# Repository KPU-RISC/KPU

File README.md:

# KPU - the RISC based Open Source CPU
This repository contains complete source code and buillding files for the KPU - a RISC based CPU (Central Processing Unit). The whole CPU is emulated, simulated, and modelled on the lowest level only with primitive AND, OR, XOR, and NOT gates.

It implements a 8-bit wide Data Bus, and a 16-bit wide Address Bus. The following 8-bit wide registers are implemented:
<ul>
<li><b>D</b> (General Purpose)</li>
<li><b>E</b> (General Purpose)</li>
<li><b>F</b> (General Purpose)</li>
<li><b>G</b> (General Purpose)</li>
<li><b>H</b> (General Purpose)</li>
<li><b>XL</b> (Lower part of the 16-bit wide "X" register</li>
<li><b>XH</b> (Upper part of the 16-bit wide "X" register</li>
</ul>

The following 16-bit wide registers are implemented:
<ul>
<li><b>SP</b> (Stack Pointer)</li>
<li><b>BP</b> (Base Pointer)</li>
<li><b>PC</b> (Program Counter)</li>
<li><b>M</b> (Memory Addressing)</li>
<li><b>J</b> (Jump Destination Addressing)</li>
<li><b>X</b> (General Purpose)</li>
<li><b>Y</b> (General Purpose)</li>
<li><b>Z</b> (General Purpose)</li>
</ul>

The project contains the following sub components:
<ul>
<li><b>Assembler</b>: The Assembler generates from the assembly language binary code that can be executed by the CPU. It is written in C#, and uses ANTLR for the syntax processing.</li>
<li><b>Emulation</b>: The C#-based Emulator is able to run binary code in a Console application or within a WinForms application (used for debugging purposes).</li>
<li><b>VHDL</b>: This folder contains the whole CPU implementation as VHDL description files.</li>
<li><b>Eagle</b>: This folder contains the whole schematics and board files ready for a physical implementation of the CPU based on 74LS TTL logic chips.</li>
<li><b>Logicly</b>: This folder contains early Proof-Of-Concept files for the Logicly simulation program.</li>
</ul>

For more detailed technical information about the CPU, please visit the project website at http://www.cpu-design.at

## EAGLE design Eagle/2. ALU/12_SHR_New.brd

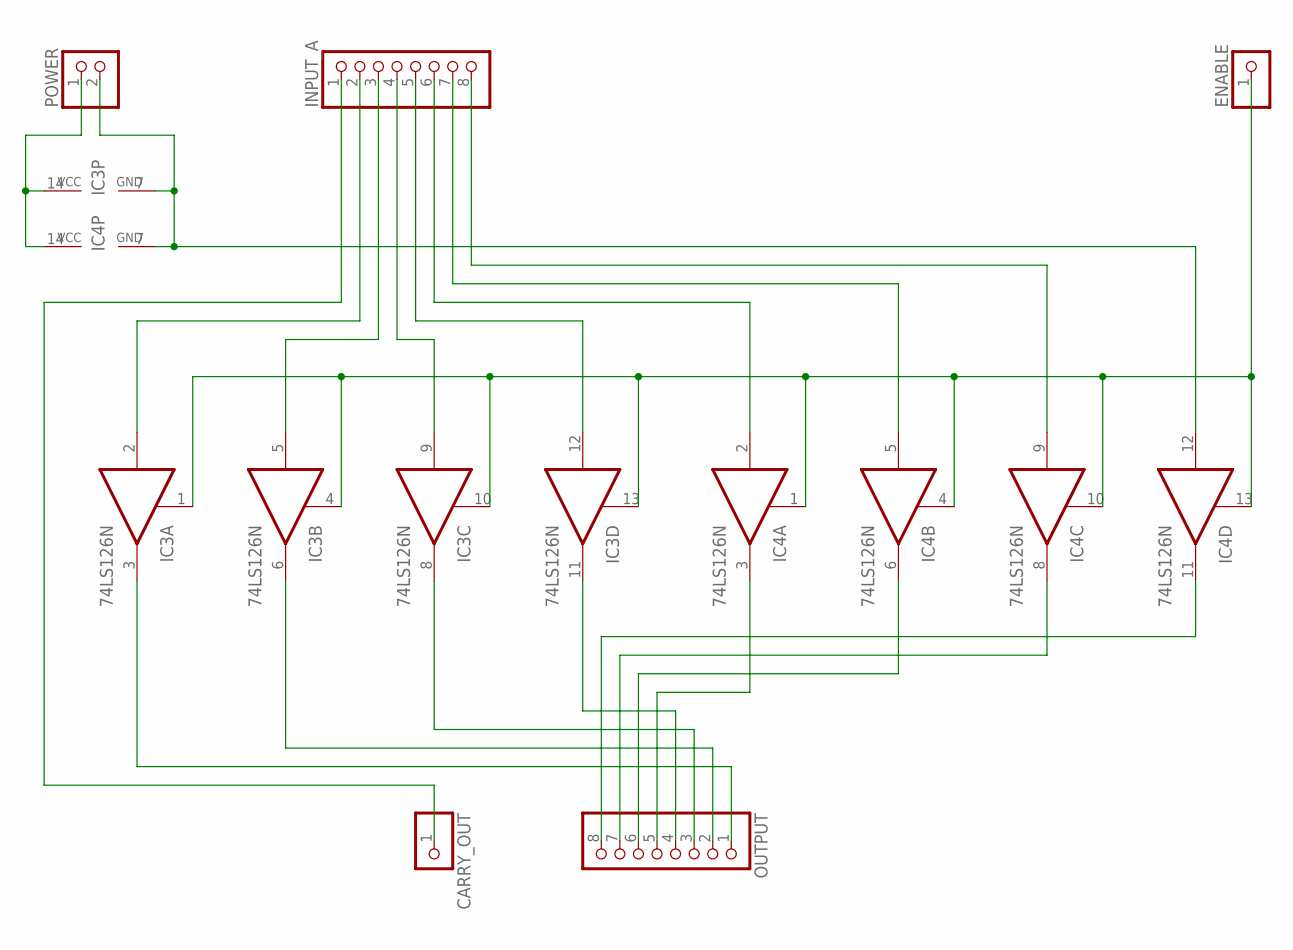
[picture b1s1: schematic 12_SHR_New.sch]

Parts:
CARRY_OUT: PINHD-1X1; 1X01
ENABLE: PINHD-1X1; 1X01
IC3, IC4: 74LS126N; DIL14
INPUT_A: PINHD-1X8; 1X08
OUTPUT: PINHD-1X8; 1X08
POWER: PINHD-1X2; 1X02

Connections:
GND: IC3.7 (GND), IC4.7 (GND), IC4.12 (I), POWER.2
unnamed: CARRY_OUT.1, INPUT_A.1
unnamed: IC3.2 (I), INPUT_A.2
unnamed: IC3.12 (I), INPUT_A.5
unnamed: IC4.2 (I), INPUT_A.6
unnamed: IC4.5 (I), INPUT_A.7
unnamed: IC4.9 (I), INPUT_A.8
unnamed: IC3.5 (I), INPUT_A.3
unnamed: IC3.9 (I), INPUT_A.4
unnamed: IC3.3 (O), OUTPUT.1
unnamed: IC3.6 (O), OUTPUT.2
unnamed: IC3.8 (O), OUTPUT.3
unnamed: IC3.11 (O), OUTPUT.4
unnamed: IC4.3 (O), OUTPUT.5
unnamed: IC4.6 (O), OUTPUT.6
unnamed: IC4.8 (O), OUTPUT.7
unnamed: IC4.11 (O), OUTPUT.8
unnamed: ENABLE.1, IC3.1 (OE), IC3.4 (OE), IC3.10 (OE), IC3.13 (OE), IC4.1 (OE), IC4.4 (OE), IC4.10 (OE), IC4.13 (OE)
VCC: IC3.14 (VCC), IC4.14 (VCC), POWER.1

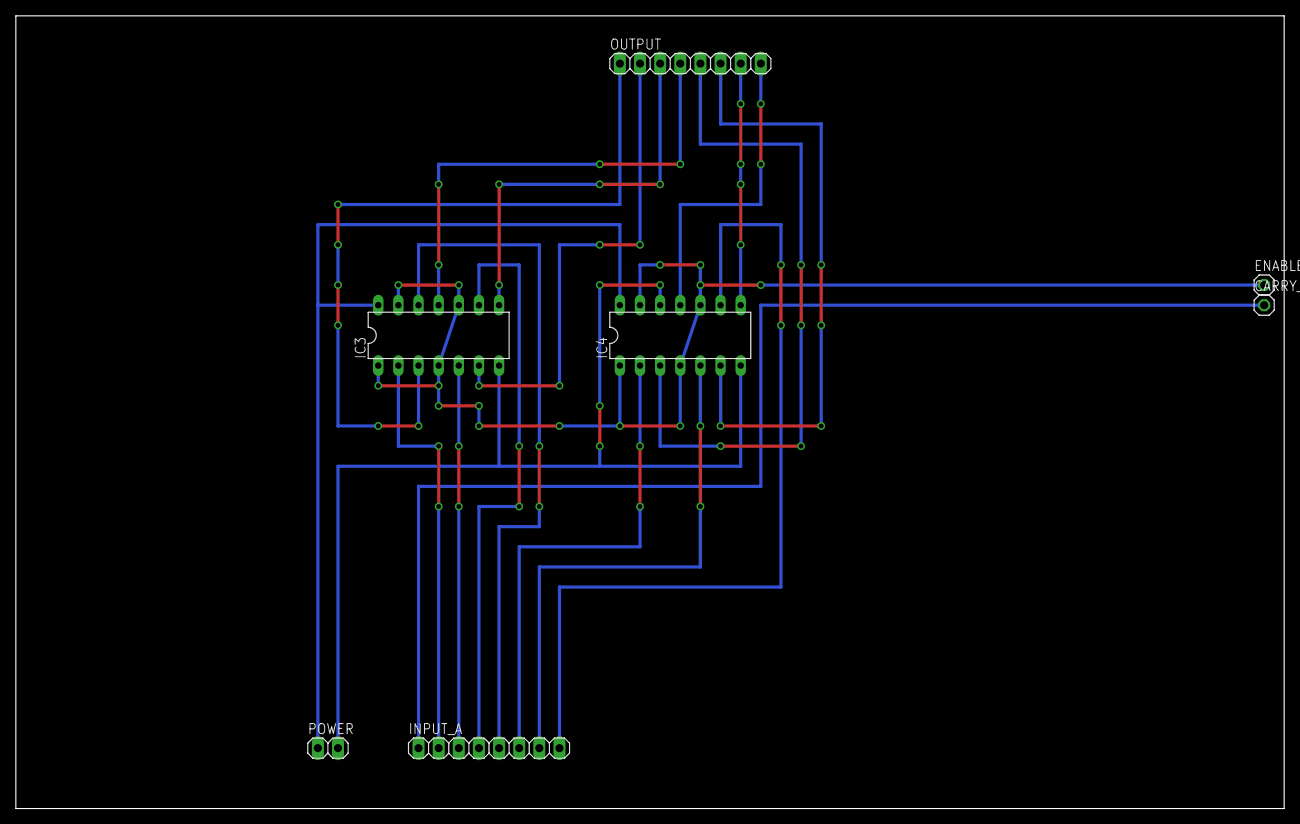
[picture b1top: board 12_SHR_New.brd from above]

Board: 2 copper layers, 160.0 x 100.0 mm, 7 parts (0 on the bottom side), 19 nets.

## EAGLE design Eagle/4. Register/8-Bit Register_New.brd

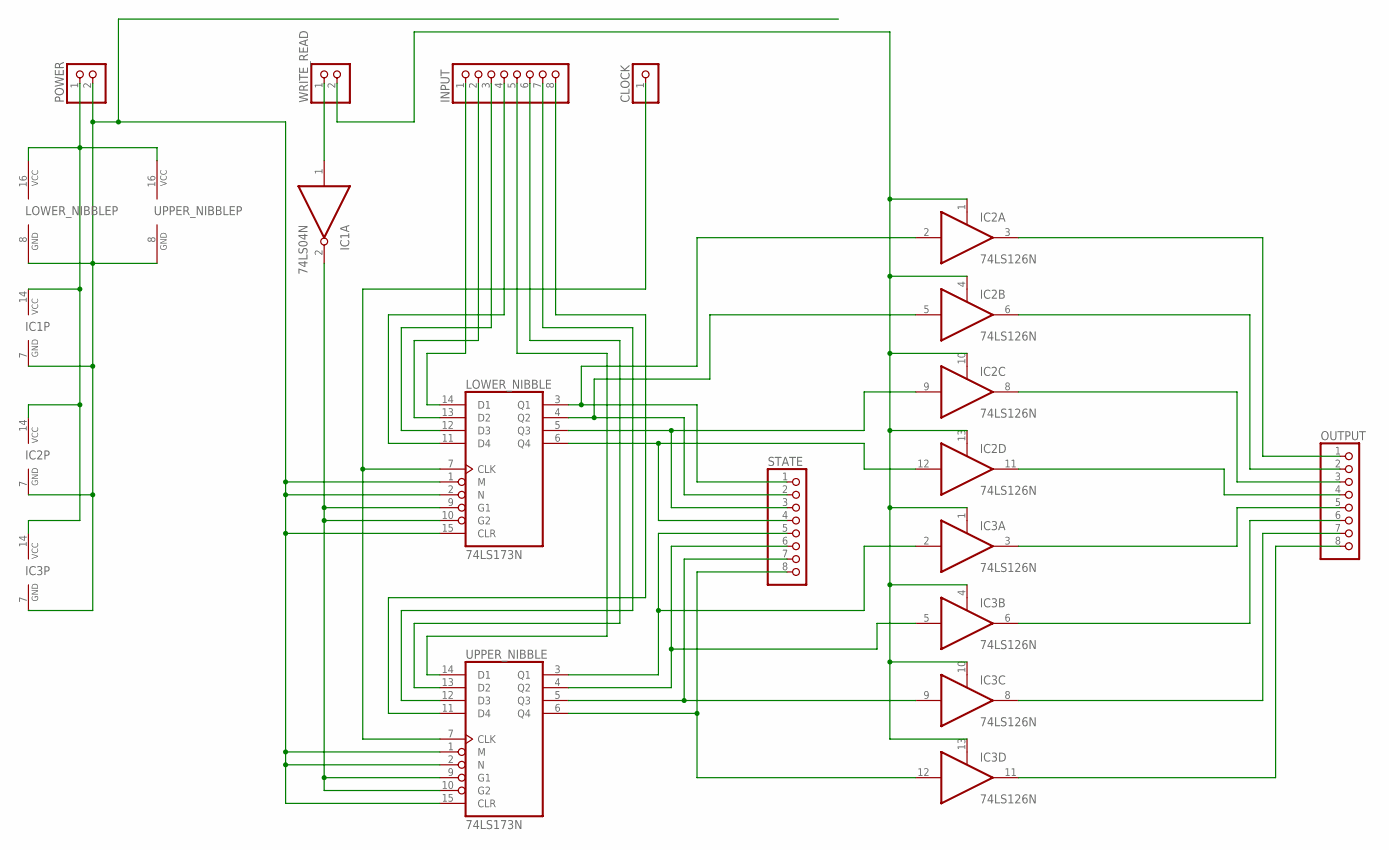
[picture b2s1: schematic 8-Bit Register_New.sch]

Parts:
CLOCK: PINHD-1X1; 1X01
IC1: 74LS04N; DIL14
IC2, IC3: 74LS126N; DIL14
INPUT: PINHD-1X8; 1X08
LOWER_NIBBLE: 74LS173N; DIL16
OUTPUT: PINHD-1X8; 1X08
POWER: PINHD-1X2; 1X02
STATE: PINHD-1X8; 1X08
UPPER_NIBBLE: 74LS173N; DIL16
WRITE_READ: PINHD-1X2; 1X02

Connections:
GND: IC1.7 (GND), IC2.7 (GND), IC3.7 (GND), LOWER_NIBBLE.1 (M), LOWER_NIBBLE.2 (N), LOWER_NIBBLE.8 (GND), LOWER_NIBBLE.15 (CLR), POWER.2, UPPER_NIBBLE.1 (M), UPPER_NIBBLE.2 (N), UPPER_NIBBLE.8 (GND), UPPER_NIBBLE.15 (CLR)
unnamed: IC2.12 (I), LOWER_NIBBLE.6 (Q4), STATE.4
unnamed: IC1.1 (I), WRITE_READ.1
unnamed: IC3.9 (I), STATE.7, UPPER_NIBBLE.5 (Q3)
unnamed: IC2.11 (O), OUTPUT.4
unnamed: IC1.2 (O), LOWER_NIBBLE.9 (G1), LOWER_NIBBLE.10 (G2), UPPER_NIBBLE.9 (G1), UPPER_NIBBLE.10 (G2)
unnamed: CLOCK.1, LOWER_NIBBLE.7 (CLK), UPPER_NIBBLE.7 (CLK)
unnamed: INPUT.1, LOWER_NIBBLE.14 (D1)
unnamed: INPUT.2, LOWER_NIBBLE.13 (D2)
unnamed: INPUT.3, LOWER_NIBBLE.12 (D3)
unnamed: INPUT.4, LOWER_NIBBLE.11 (D4)
unnamed: INPUT.6, UPPER_NIBBLE.13 (D2)
unnamed: INPUT.5, UPPER_NIBBLE.14 (D1)
unnamed: INPUT.7, UPPER_NIBBLE.12 (D3)
unnamed: INPUT.8, UPPER_NIBBLE.11 (D4)
unnamed: IC2.2 (I), LOWER_NIBBLE.3 (Q1), STATE.1
unnamed: IC2.5 (I), LOWER_NIBBLE.4 (Q2), STATE.2
unnamed: IC2.9 (I), LOWER_NIBBLE.5 (Q3), STATE.3
unnamed: IC3.2 (I), STATE.5, UPPER_NIBBLE.3 (Q1)
unnamed: IC3.5 (I), STATE.6, UPPER_NIBBLE.4 (Q2)
unnamed: IC3.12 (I), STATE.8, UPPER_NIBBLE.6 (Q4)
unnamed: IC2.1 (OE), IC2.4 (OE), IC2.10 (OE), IC2.13 (OE), IC3.1 (OE), IC3.4 (OE), IC3.10 (OE), IC3.13 (OE), WRITE_READ.2
unnamed: IC2.3 (O), OUTPUT.1
unnamed: IC2.6 (O), OUTPUT.2
unnamed: IC2.8 (O), OUTPUT.3
unnamed: IC3.3 (O), OUTPUT.5
unnamed: IC3.6 (O), OUTPUT.6
unnamed: IC3.8 (O), OUTPUT.7
unnamed: IC3.11 (O), OUTPUT.8
VCC: IC1.14 (VCC), IC2.14 (VCC), IC3.14 (VCC), LOWER_NIBBLE.16 (VCC), POWER.1, UPPER_NIBBLE.16 (VCC)

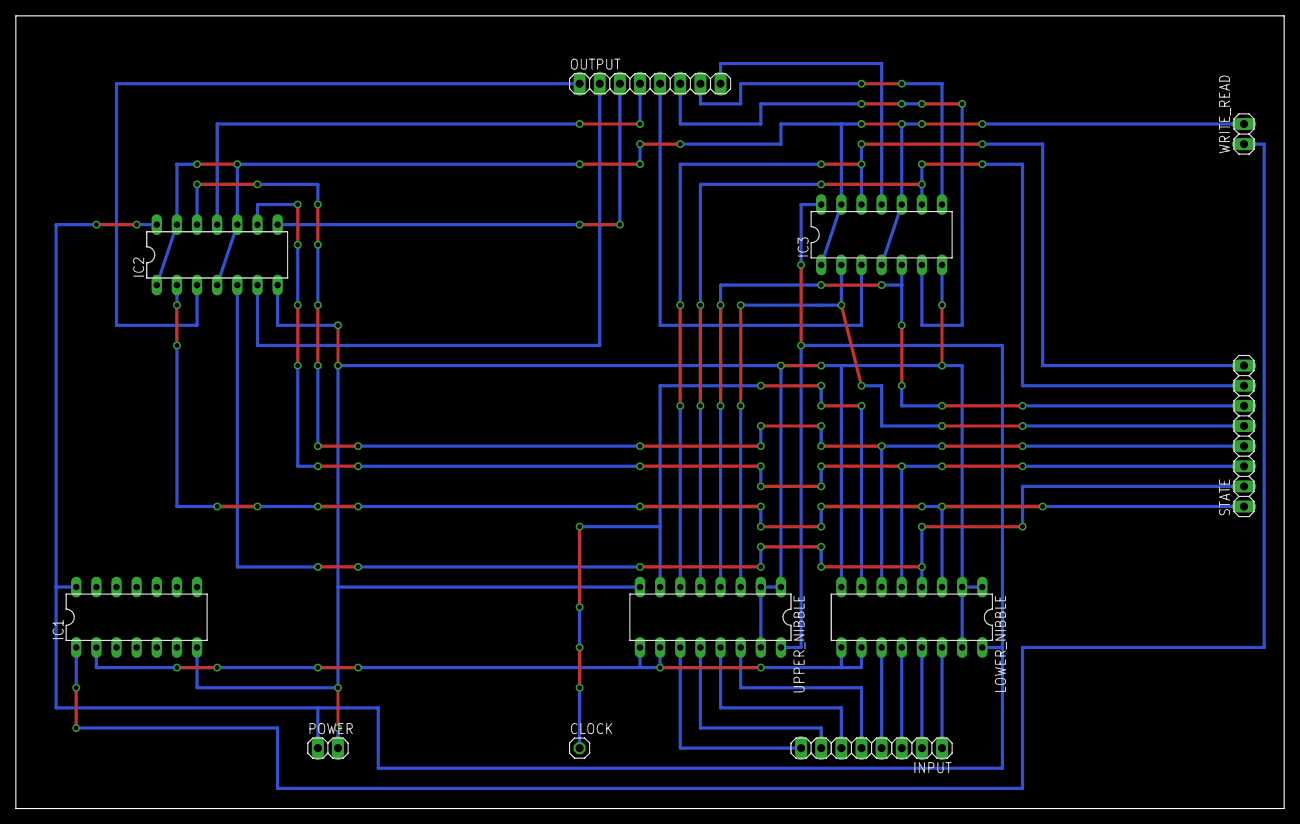
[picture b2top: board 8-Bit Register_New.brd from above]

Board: 2 copper layers, 160.0 x 100.0 mm, 11 parts (0 on the bottom side), 30 nets.

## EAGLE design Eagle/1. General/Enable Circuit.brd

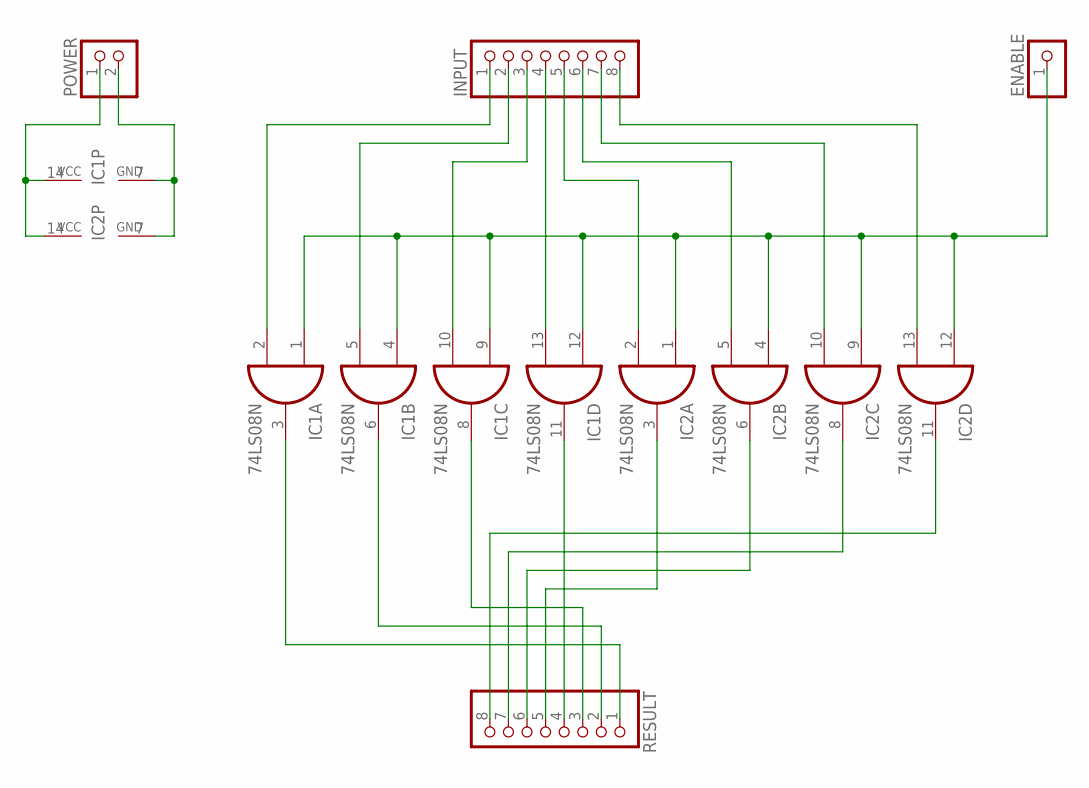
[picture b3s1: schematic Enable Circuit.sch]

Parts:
ENABLE: PINHD-1X1; 1X01
IC1, IC2: 74LS08N; DIL14
INPUT: PINHD-1X8; 1X08
POWER: PINHD-1X2; 1X02
RESULT: PINHD-1X8; 1X08

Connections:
GND: IC1.7 (GND), IC2.7 (GND), POWER.2
unnamed: IC1.2 (I1), INPUT.1
unnamed: IC1.5 (I1), INPUT.2
unnamed: IC1.10 (I1), INPUT.3
unnamed: IC1.13 (I1), INPUT.4
unnamed: IC2.2 (I1), INPUT.5
unnamed: IC2.5 (I1), INPUT.6
unnamed: IC2.10 (I1), INPUT.7
unnamed: IC2.13 (I1), INPUT.8
unnamed: ENABLE.1, IC1.1 (I0), IC1.4 (I0), IC1.9 (I0), IC1.12 (I0), IC2.1 (I0), IC2.4 (I0), IC2.9 (I0), IC2.12 (I0)
unnamed: IC1.3 (O), RESULT.1
unnamed: IC1.6 (O), RESULT.2
unnamed: IC1.8 (O), RESULT.3
unnamed: IC1.11 (O), RESULT.4
unnamed: IC2.3 (O), RESULT.5
unnamed: IC2.6 (O), RESULT.6
unnamed: IC2.8 (O), RESULT.7
unnamed: IC2.11 (O), RESULT.8
VCC: IC1.14 (VCC), IC2.14 (VCC), POWER.1

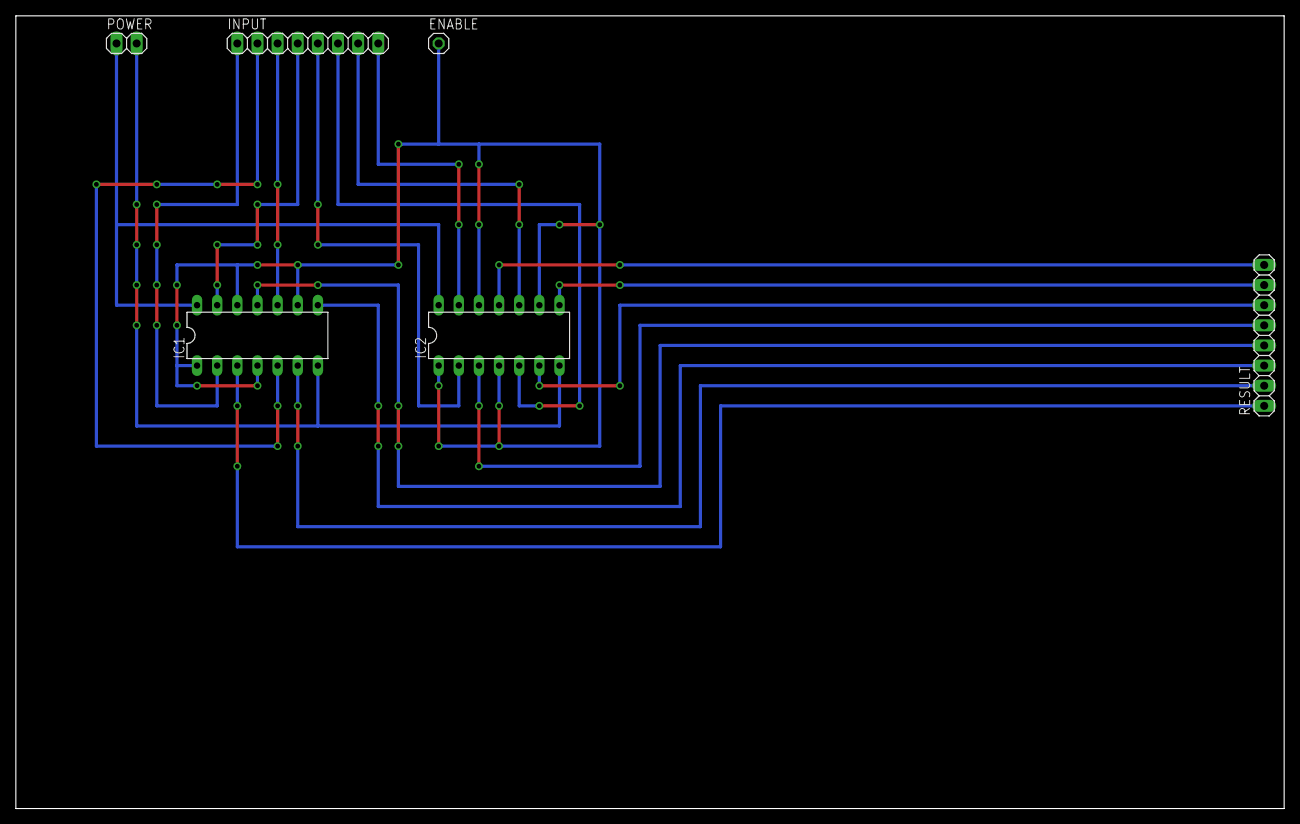
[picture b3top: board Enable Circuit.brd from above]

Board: 2 copper layers, 160.0 x 100.0 mm, 6 parts (0 on the bottom side), 19 nets.

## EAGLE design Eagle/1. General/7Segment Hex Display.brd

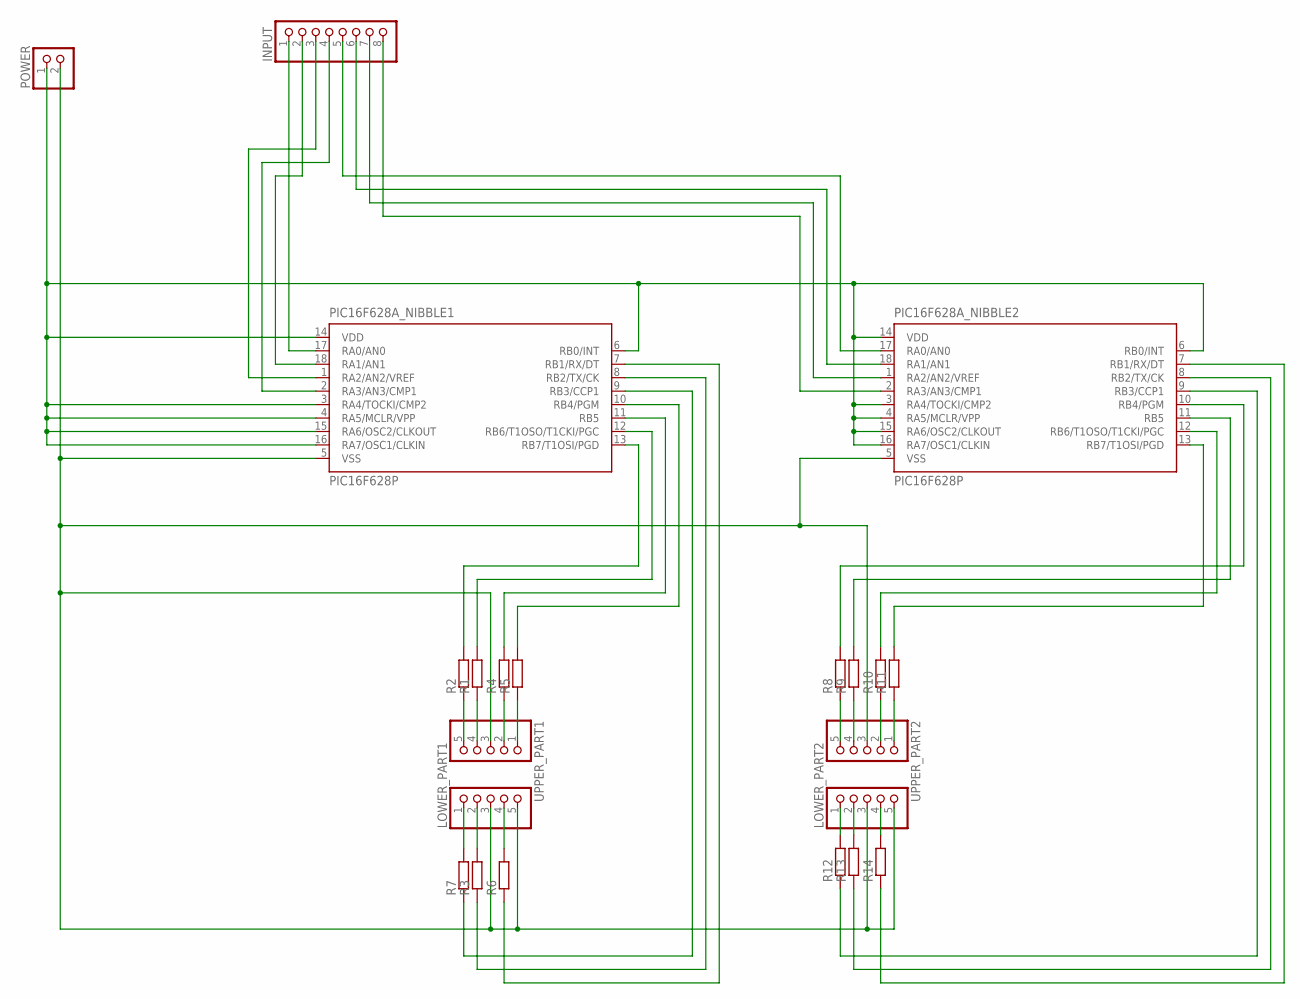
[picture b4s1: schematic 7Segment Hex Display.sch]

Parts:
INPUT: PINHD-1X8; 1X08
LOWER_PART1, LOWER_PART2: PINHD-1X5; 1X05
PIC16F628A_NIBBLE1, PIC16F628A_NIBBLE2: PIC16F628P; DIL18
POWER: PINHD-1X2; 1X02
R1, R2, R3, R4, R5, R6, R7, R8, R9, R10, R11, R12, R13, R14: R-EU_0207/10; 0207/10
UPPER_PART1, UPPER_PART2: PINHD-1X5; 1X05

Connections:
unnamed: INPUT.3, PIC16F628A_NIBBLE1.1 (RA2/AN2/VREF)
unnamed: INPUT.4, PIC16F628A_NIBBLE1.2 (RA3/AN3/CMP1)
unnamed: R2.1, UPPER_PART1.5
unnamed: PIC16F628A_NIBBLE1.13 (RB7/T1OSI/PGD), R2.2
unnamed: INPUT.2, PIC16F628A_NIBBLE1.18 (RA1/AN1)
unnamed: INPUT.1, PIC16F628A_NIBBLE1.17 (RA0/AN0)
unnamed: PIC16F628A_NIBBLE1.3 (RA4/TOCKI/CMP2), PIC16F628A_NIBBLE1.4 (RA5/MCLR/VPP), PIC16F628A_NIBBLE1.6 (RB0/INT), PIC16F628A_NIBBLE1.14 (VDD), PIC16F628A_NIBBLE1.15 (RA6/OSC2/CLKOUT), PIC16F628A_NIBBLE1.16 (RA7/OSC1/CLKIN), PIC16F628A_NIBBLE2.3 (RA4/TOCKI/CMP2), PIC16F628A_NIBBLE2.4 (RA5/MCLR/VPP), PIC16F628A_NIBBLE2.6 (RB0/INT), PIC16F628A_NIBBLE2.14 (VDD), PIC16F628A_NIBBLE2.15 (RA6/OSC2/CLKOUT), PIC16F628A_NIBBLE2.16 (RA7/OSC1/CLKIN), POWER.1
unnamed: LOWER_PART1.3, LOWER_PART1.5, LOWER_PART2.3, LOWER_PART2.5, PIC16F628A_NIBBLE1.5 (VSS), PIC16F628A_NIBBLE2.5 (VSS), POWER.2, UPPER_PART1.3, UPPER_PART2.3
unnamed: PIC16F628A_NIBBLE1.12 (RB6/T1OSO/T1CKI/PGC), R1.2
unnamed: R1.1, UPPER_PART1.4
unnamed: PIC16F628A_NIBBLE1.8 (RB2/TX/CK), R3.1
unnamed: PIC16F628A_NIBBLE1.11 (RB5), R4.2
unnamed: PIC16F628A_NIBBLE1.10 (RB4/PGM), R5.2
unnamed: LOWER_PART1.2, R3.2
unnamed: R4.1, UPPER_PART1.2
unnamed: R5.1, UPPER_PART1.1
unnamed: PIC16F628A_NIBBLE1.9 (RB3/CCP1), R7.1
unnamed: LOWER_PART1.1, R7.2
unnamed: PIC16F628A_NIBBLE2.7 (RB1/RX/DT), R14.1
unnamed: PIC16F628A_NIBBLE1.7 (RB1/RX/DT), R6.1
unnamed: LOWER_PART1.4, R6.2
unnamed: R8.1, UPPER_PART2.5
unnamed: INPUT.5, PIC16F628A_NIBBLE2.17 (RA0/AN0)
unnamed: INPUT.6, PIC16F628A_NIBBLE2.18 (RA1/AN1)
unnamed: INPUT.7, PIC16F628A_NIBBLE2.1 (RA2/AN2/VREF)
unnamed: INPUT.8, PIC16F628A_NIBBLE2.2 (RA3/AN3/CMP1)
unnamed: R9.1, UPPER_PART2.4
unnamed: R10.1, UPPER_PART2.2
unnamed: R11.1, UPPER_PART2.1
unnamed: LOWER_PART2.1, R12.2
unnamed: LOWER_PART2.2, R13.2
unnamed: LOWER_PART2.4, R14.2
unnamed: PIC16F628A_NIBBLE2.13 (RB7/T1OSI/PGD), R11.2
unnamed: PIC16F628A_NIBBLE2.12 (RB6/T1OSO/T1CKI/PGC), R10.2
unnamed: PIC16F628A_NIBBLE2.11 (RB5), R9.2
unnamed: PIC16F628A_NIBBLE2.10 (RB4/PGM), R8.2
unnamed: PIC16F628A_NIBBLE2.9 (RB3/CCP1), R12.1
unnamed: PIC16F628A_NIBBLE2.8 (RB2/TX/CK), R13.1

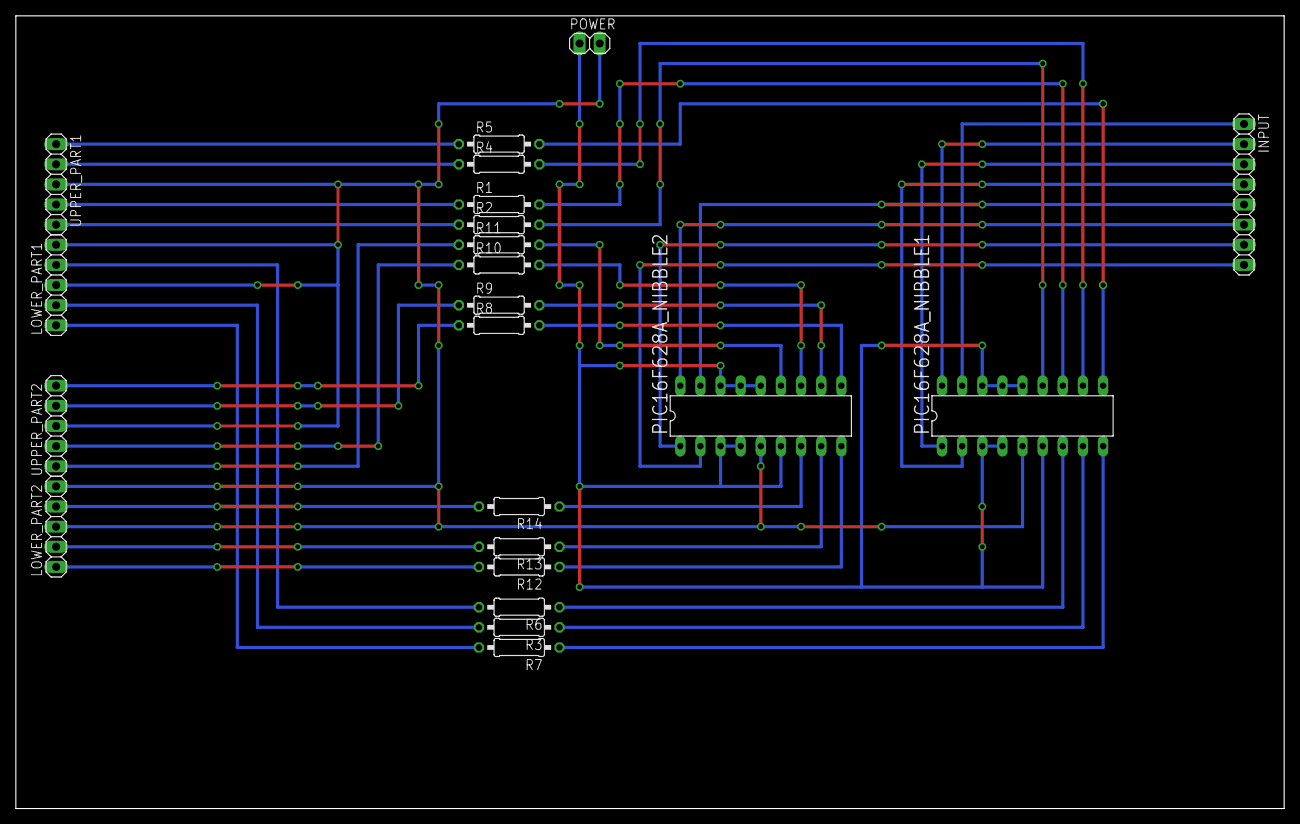
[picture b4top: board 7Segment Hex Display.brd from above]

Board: 2 copper layers, 160.0 x 100.0 mm, 22 parts (0 on the bottom side), 38 nets.

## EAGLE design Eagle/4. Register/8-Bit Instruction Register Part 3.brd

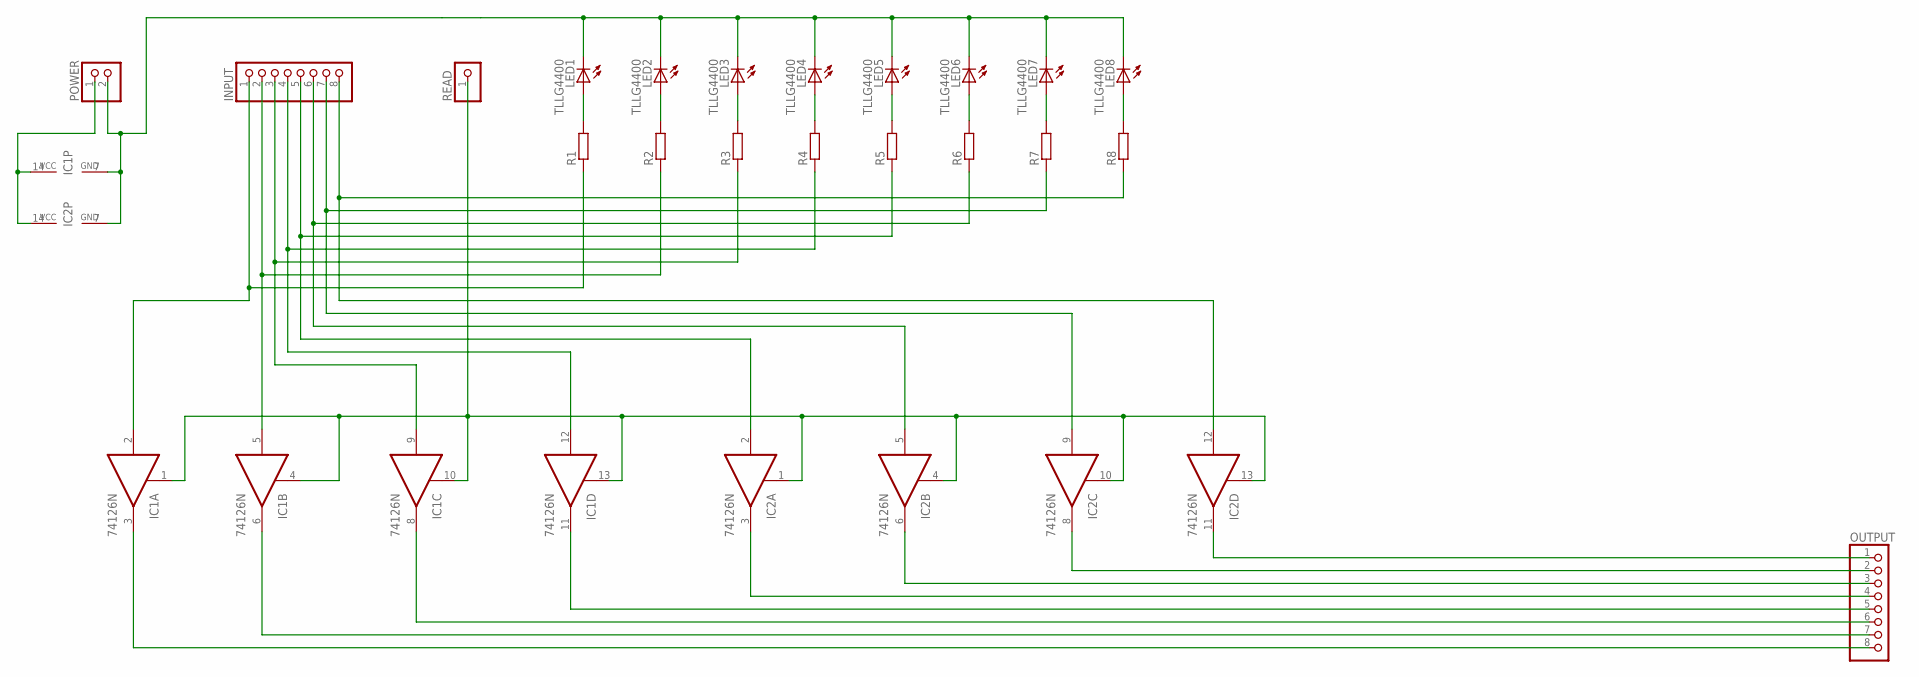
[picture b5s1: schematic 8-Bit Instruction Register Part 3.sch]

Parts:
IC1, IC2: 74126N; DIL14
INPUT: PINHD-1X8; 1X08
LED1, LED2, LED3, LED4, LED5, LED6, LED7, LED8: TLLG4400; LED3MM
OUTPUT: PINHD-1X8; 1X08
POWER: PINHD-1X2; 1X02
R1, R2, R3, R4, R5, R6, R7, R8: R-EU_0207/7; 0207/7
READ: PINHD-1X1; 1X01

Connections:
GND: IC1.7 (GND), IC2.7 (GND), LED1.K (C), LED2.K (C), LED3.K (C), LED4.K (C), LED5.K (C), LED6.K (C), LED7.K (C), LED8.K (C), POWER.2
unnamed: IC1.2 (I), INPUT.1, R1.1
unnamed: IC1.5 (I), INPUT.2, R2.1
unnamed: IC1.9 (I), INPUT.3, R3.1
unnamed: IC1.12 (I), INPUT.4, R4.1
unnamed: IC2.2 (I), INPUT.5, R5.1
unnamed: IC2.5 (I), INPUT.6, R6.1
unnamed: IC2.9 (I), INPUT.7, R7.1
unnamed: IC2.12 (I), INPUT.8, R8.1
unnamed: LED1.A, R1.2
unnamed: IC1.1 (OE), IC1.4 (OE), IC1.10 (OE), IC1.13 (OE), IC2.1 (OE), IC2.4 (OE), IC2.10 (OE), IC2.13 (OE), READ.1
unnamed: IC1.3 (O), OUTPUT.8
unnamed: IC1.6 (O), OUTPUT.7
unnamed: IC1.8 (O), OUTPUT.6
unnamed: IC1.11 (O), OUTPUT.5
unnamed: IC2.3 (O), OUTPUT.4
unnamed: IC2.6 (O), OUTPUT.3
unnamed: IC2.8 (O), OUTPUT.2
unnamed: IC2.11 (O), OUTPUT.1
unnamed: LED2.A, R2.2
unnamed: LED3.A, R3.2
unnamed: LED4.A, R4.2
unnamed: LED5.A, R5.2
unnamed: LED6.A, R6.2
unnamed: LED7.A, R7.2
unnamed: LED8.A, R8.2
VCC: IC1.14 (VCC), IC2.14 (VCC), POWER.1

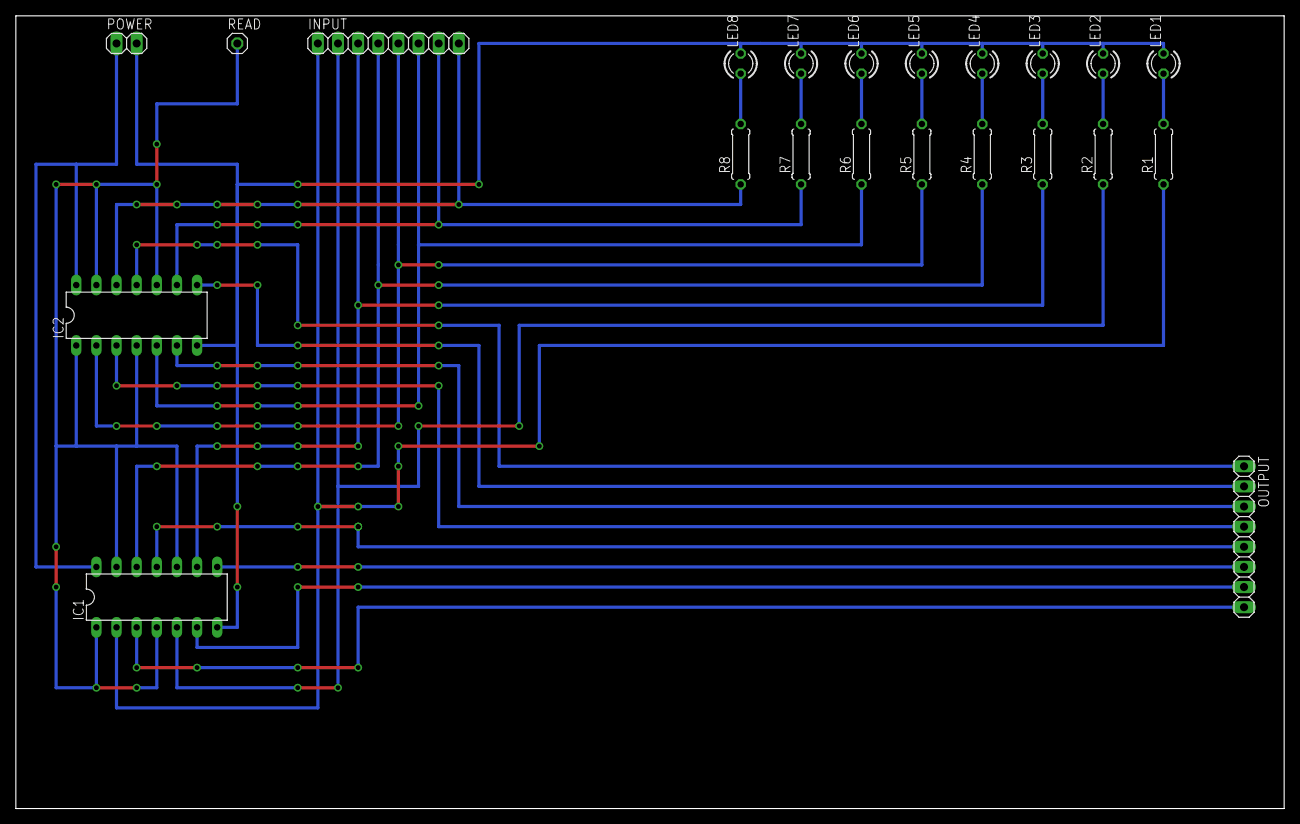
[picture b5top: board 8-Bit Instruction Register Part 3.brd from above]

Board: 2 copper layers, 160.0 x 100.0 mm, 22 parts (0 on the bottom side), 27 nets.

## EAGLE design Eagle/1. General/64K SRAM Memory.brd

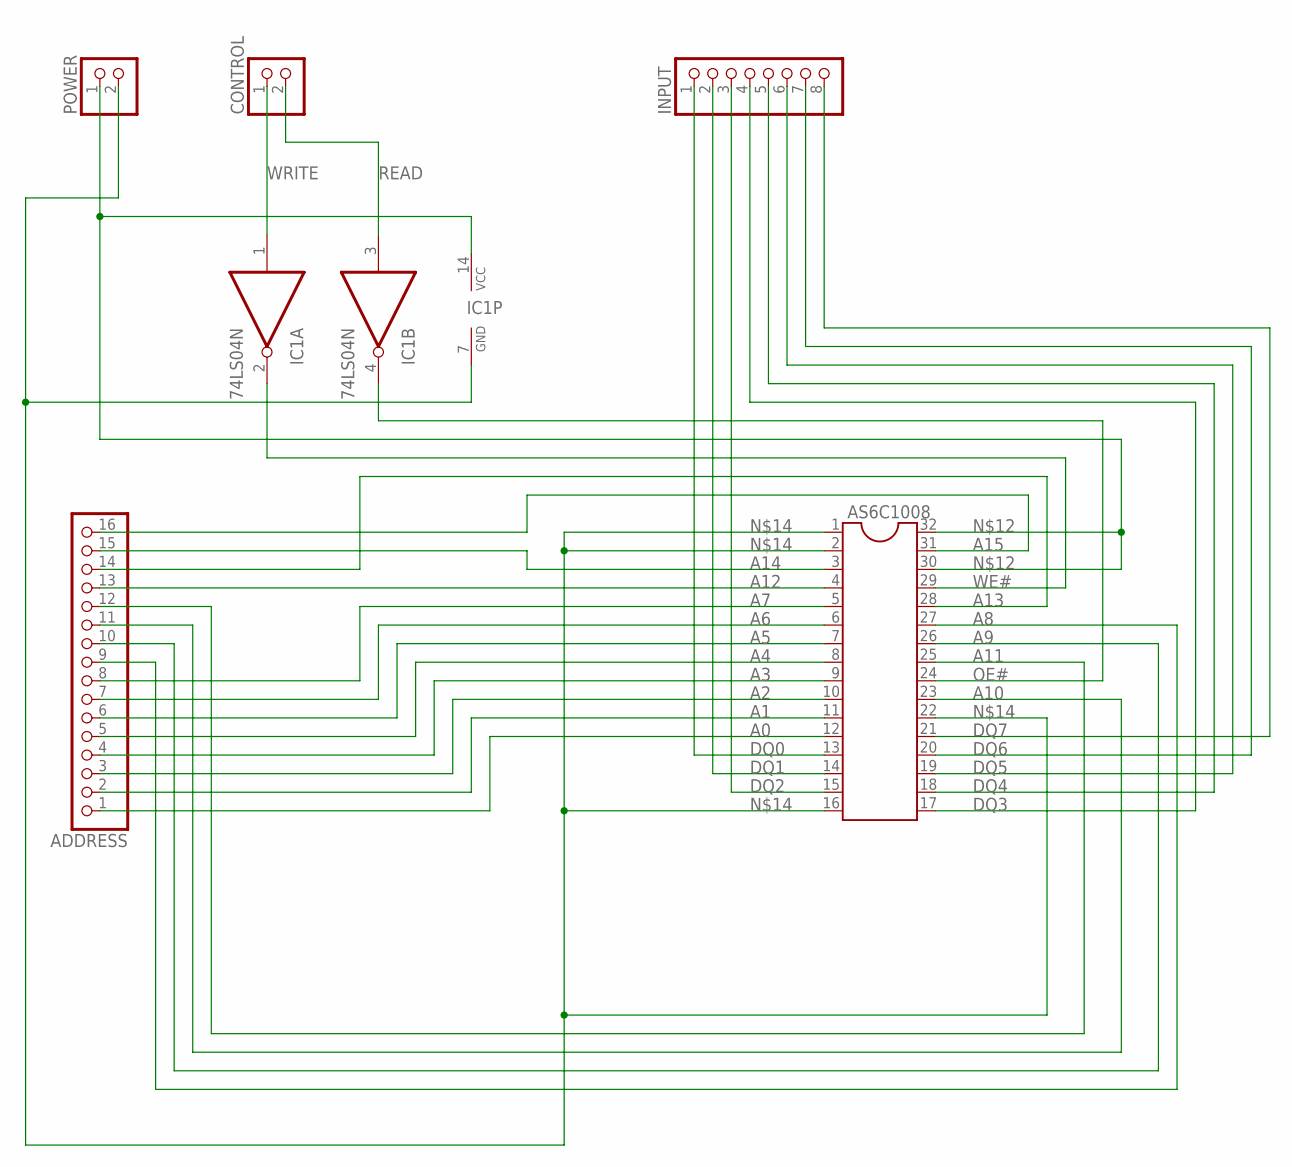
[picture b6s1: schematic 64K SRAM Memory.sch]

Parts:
ADDRESS: PINHD-1X16; 1X16
AS6C1008: DIL32
CONTROL: PINHD-1X2; 1X02
IC1: 74LS04N; DIL14
INPUT: PINHD-1X8; 1X08
POWER: PINHD-1X2; 1X02

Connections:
A0: ADDRESS.1, AS6C1008.12
A1: ADDRESS.2, AS6C1008.11
A2: ADDRESS.3, AS6C1008.10
A3: ADDRESS.4, AS6C1008.9
A4: ADDRESS.5, AS6C1008.8
A5: ADDRESS.6, AS6C1008.7
A6: ADDRESS.7, AS6C1008.6
A7: ADDRESS.8, AS6C1008.5
A8: ADDRESS.9, AS6C1008.27
A9: ADDRESS.10, AS6C1008.26
A10: ADDRESS.11, AS6C1008.23
A11: ADDRESS.12, AS6C1008.25
A12: ADDRESS.13, AS6C1008.4
A13: ADDRESS.14, AS6C1008.28
A14: ADDRESS.15, AS6C1008.3
A15: ADDRESS.16, AS6C1008.31
DQ0: AS6C1008.13, INPUT.1
DQ1: AS6C1008.14, INPUT.2
DQ2: AS6C1008.15, INPUT.3
DQ3: AS6C1008.17, INPUT.4
DQ4: AS6C1008.18, INPUT.5
DQ5: AS6C1008.19, INPUT.6
DQ6: AS6C1008.20, INPUT.7
DQ7: AS6C1008.21, INPUT.8
unnamed: AS6C1008.30, AS6C1008.32, IC1.14 (VCC), POWER.1
unnamed: AS6C1008.1, AS6C1008.2, AS6C1008.16, AS6C1008.22, IC1.7 (GND), POWER.2
OE#: AS6C1008.24, IC1.4 (O)
READ: CONTROL.2, IC1.3 (I)
WE#: AS6C1008.29, IC1.2 (O)
WRITE: CONTROL.1, IC1.1 (I)

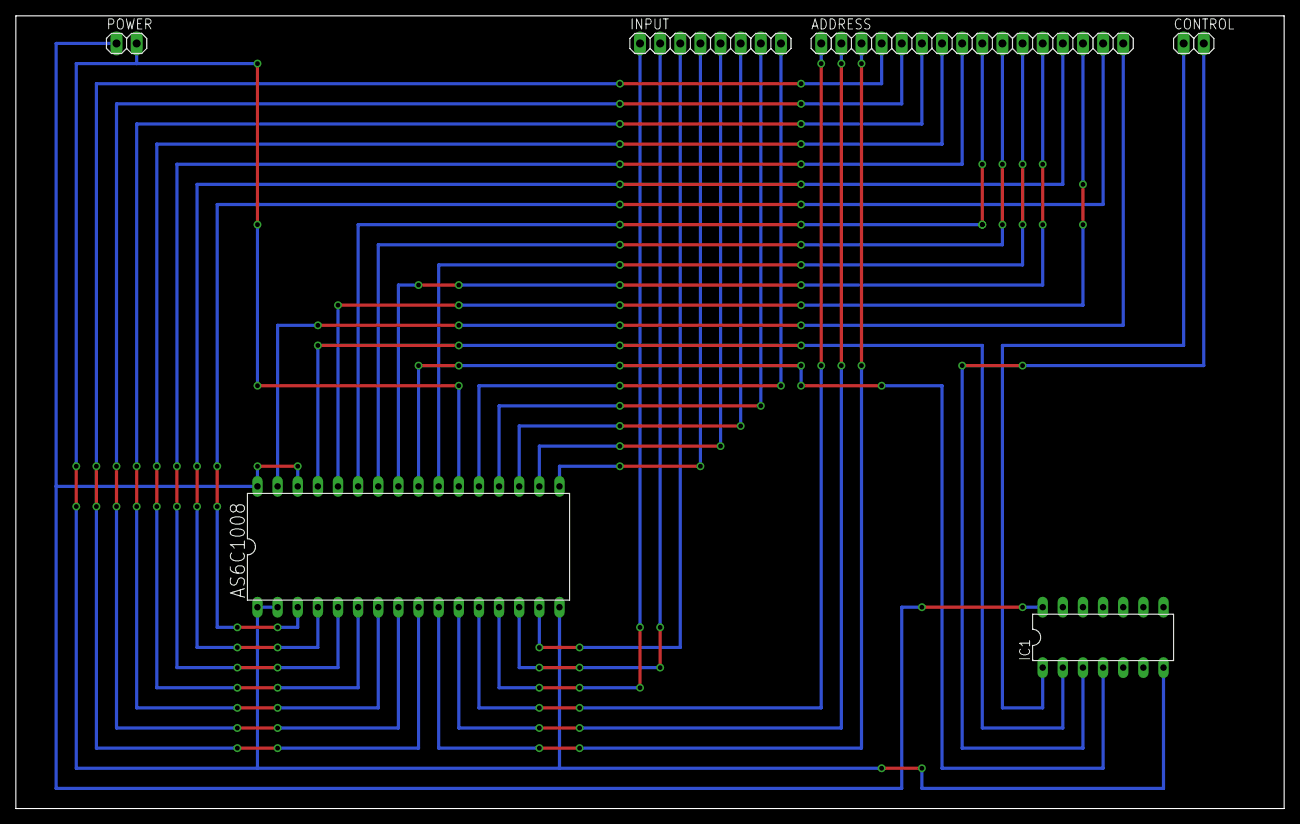
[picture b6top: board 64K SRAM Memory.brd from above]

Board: 2 copper layers, 160.0 x 100.0 mm, 6 parts (0 on the bottom side), 30 nets.

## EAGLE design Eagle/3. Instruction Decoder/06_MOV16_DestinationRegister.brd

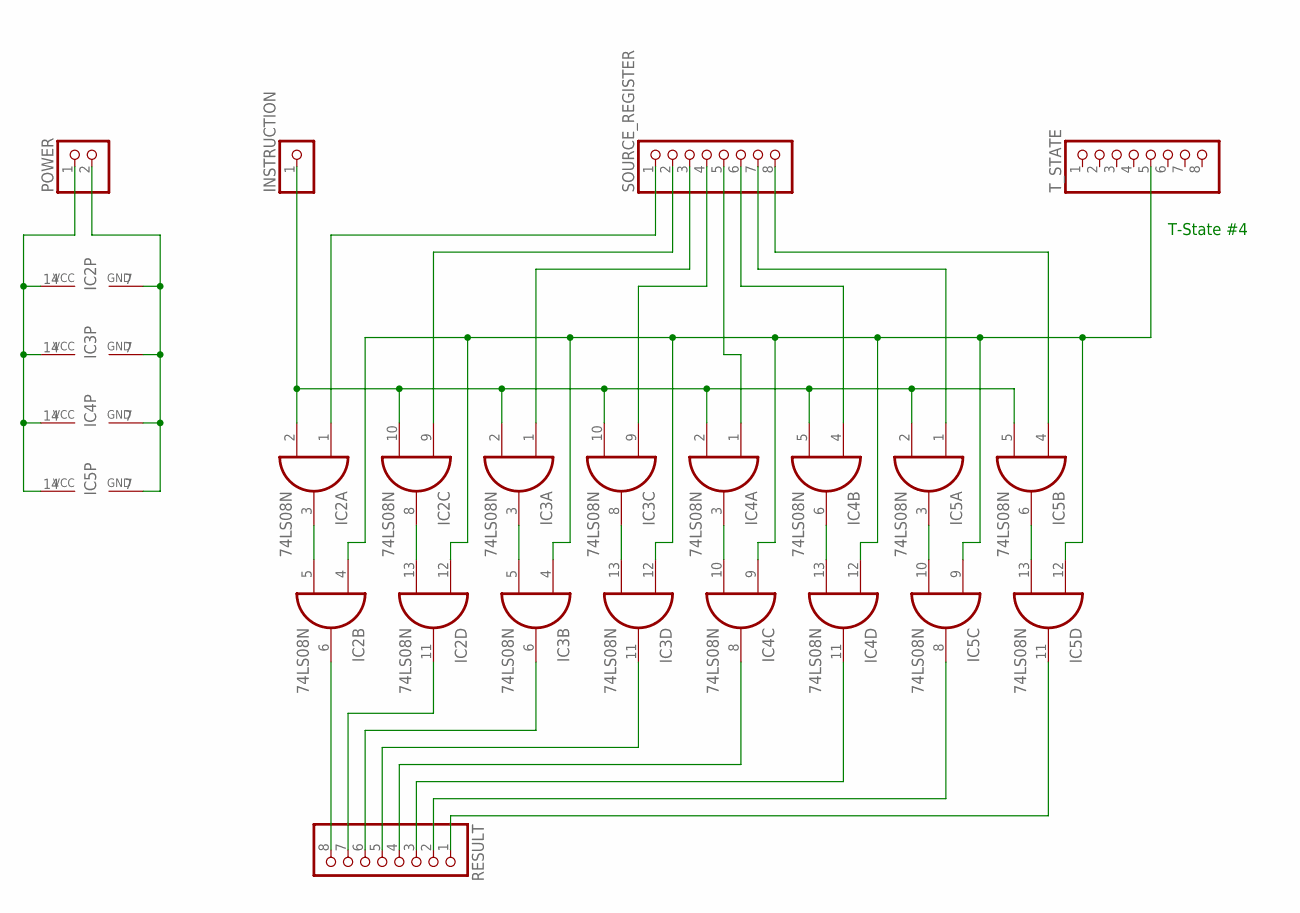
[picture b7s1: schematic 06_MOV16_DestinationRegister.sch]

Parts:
IC2, IC3, IC4, IC5: 74LS08N; DIL14
INSTRUCTION: PINHD-1X1; 1X01
POWER: PINHD-1X2; 1X02
RESULT: PINHD-1X8; 1X08
SOURCE_REGISTER: PINHD-1X8; 1X08
T_STATE: PINHD-1X8; 1X08

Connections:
GND: IC2.7 (GND), IC3.7 (GND), IC4.7 (GND), IC5.7 (GND), POWER.2
unnamed: IC2.4 (I0), IC2.12 (I0), IC3.4 (I0), IC3.12 (I0), IC4.9 (I0), IC4.12 (I0), IC5.9 (I0), IC5.12 (I0), T_STATE.5
unnamed: IC2.2 (I1), IC2.10 (I1), IC3.2 (I1), IC3.10 (I1), IC4.2 (I1), IC4.5 (I1), IC5.2 (I1), IC5.5 (I1), INSTRUCTION.1
unnamed: IC2.1 (I0), SOURCE_REGISTER.1
unnamed: IC2.3 (O), IC2.5 (I1)
unnamed: IC2.6 (O), RESULT.8
unnamed: IC2.9 (I0), SOURCE_REGISTER.2
unnamed: IC2.8 (O), IC2.13 (I1)
unnamed: IC3.1 (I0), SOURCE_REGISTER.3
unnamed: IC2.11 (O), RESULT.7
unnamed: IC3.3 (O), IC3.5 (I1)
unnamed: IC3.6 (O), RESULT.6
unnamed: IC3.9 (I0), SOURCE_REGISTER.4
unnamed: IC3.8 (O), IC3.13 (I1)
unnamed: IC3.11 (O), RESULT.5
unnamed: IC4.1 (I0), SOURCE_REGISTER.5
unnamed: IC4.3 (O), IC4.10 (I1)
unnamed: IC4.8 (O), RESULT.4
unnamed: IC4.4 (I0), SOURCE_REGISTER.6
unnamed: IC4.6 (O), IC4.13 (I1)
unnamed: IC4.11 (O), RESULT.3
unnamed: IC5.1 (I0), SOURCE_REGISTER.7
unnamed: IC5.3 (O), IC5.10 (I1)
unnamed: IC5.8 (O), RESULT.2
unnamed: IC5.4 (I0), SOURCE_REGISTER.8
unnamed: IC5.6 (O), IC5.13 (I1)
unnamed: IC5.11 (O), RESULT.1
VCC: IC2.14 (VCC), IC3.14 (VCC), IC4.14 (VCC), IC5.14 (VCC), POWER.1

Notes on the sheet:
T-State #4
